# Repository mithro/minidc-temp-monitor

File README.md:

# minidc-temp-monitor

> [!CAUTION]
> **AI in use, use at own risk.**

Cheap temperature monitoring for a **miniature datacenter** with a hot aisle
and a cold aisle. A 42&nbsp;x&nbsp;13 mm **sensor strip board** carries a WCH
RISC-V microcontroller (**CH32V003** or **CH32V005**) and a 100 k NTC
thermistor, with a **JST SH 4-pin** (Qwiic / STEMMA QT style) connector at
each end. Boards daisy-chain on stock cables, and a hub reads the whole chain
over I2C from one end.

A board's address is its position in the chain, so there are no address
straps and the hub sees the boards in their physical order. In a 240-board
build at JLCPCB each board costs $0.30 to $0.33 in parts and $0.58 to $0.97
assembled, before shipping and tax, with the assembly fees calculated from
JLCPCB's published rates.

| `sensor-ch32v003` (SOP-8) | `sensor-ch32v005` (QFN-12) |
| --- | --- |
|  |  |

The KiCad 9 projects are `hardware/sensor-ch32v003` and
`hardware/sensor-ch32v005`. Each has the panel gerbers, parts list and
placement file for an order in `out/panel/`.

Contents:

* [Status](#status)
* [How the chain works](#how-the-chain-works)
* [The two boards](#the-two-boards)
* [What you need](#what-you-need)
* [Getting the boards made](#getting-the-boards-made)
* [Putting a chain together](#putting-a-chain-together)
* [Reading temperatures](#reading-temperatures)
* [Rebuilding the files](#rebuilding-the-files)
* [Further reading](#further-reading)

## Status

| Part | State |
| --- | --- |
| Sensor strip board, v0.2, both versions | drawn, passes ERC and DRC, **not yet built** |
| 16-board assembly panel | drawn, accepted by JLCPCB's and NextPCB's quote pages, not ordered |
| Relay firmware and I2C bootloader | build for both boards and pass tests in a simulated chain, **not yet run on a board** |
| Hub library and command line (`minidc.py`) | tested against the simulated chain only |
| Hub hardware | not designed |
| Humidity sensing | not designed |

Still open: the cable length per aisle and the number of sensor points per
rack face. The known gaps of the board are listed in
[hardware/README.md](hardware/README.md#known-gaps-in-v02), and what the
firmware tests do and do not cover in
[firmware/README.md](firmware/README.md#what-has-been-tested).

## How the chain works

Every cable is its own short I2C bus. On its upstream connector (**J1, UP**) a
board is an I2C target at address `0x2A`. On its downstream connector
(**J2, DN**) it is a bit-banged I2C controller talking to the next board. All
boards use the same address, because each one is alone on its hop.

* **Addressing.** Each command carries a hop count. A board that gets a
  command with a count above zero takes one off and passes it on, and the
  board that sees zero carries it out. Board 0 is the one plugged into the
  hub.
* **Temperatures.** One command reads up to 16 boards in one go, in 0.01 C
  steps. The reading is a ratio of the supply, so it is the same at 3.3 V
  and 5 V.
* **Identify LED.** A command turns on or blinks the LED of one board, to
  find it in the rack.
* **Updates.** Boards take new firmware over the same cable through an I2C
  bootloader, one board at a time.
* **Supply.** 3.3 V or 5 V, passed straight through the chain with no
  regulator on the boards. Never more than 5.5 V.

Because each hop is a fresh bus, cable length does not add up along a chain.
The protocol, the bootloader and the timings are in
[firmware/README.md](firmware/README.md). A shared pass-through bus is a
fitting option on the board
([chain wiring option](hardware/README.md#chain-wiring-option)); the firmware
here is for the relay fitting.

## The two boards

Both versions share the outline, the connectors and every part except the
microcontroller.

| | `sensor-ch32v003` | `sensor-ch32v005` |
| --- | --- | --- |
| Microcontroller | CH32V003J4M6, SOP-8 | CH32V005D6U6, QFN-12 2&nbsp;x&nbsp;2 mm |
| ADC | 10 bit | 12 bit |
| Programming | SWIO test pad | SWIO shares the SCL pin of J1, or the test pad |
| Spare pins | none | two GPIOs and reset on pads |
| Board finish costed | lead-free HASL | ENIG |
| Parts per board | $0.33 | $0.30 |
| 240 boards assembled, JLCPCB | $140 | $233, with X-ray inspection |
| 240 boards assembled, NextPCB | $529 | $651 |

The board has a 3.2 mm hole for an M3 screw, a waist for a zip tie and a flat
back for an adhesive pad or a glued magnet. The thermistor sits on a finger
cut free of the rest of the board. Dimensions, pin use, the copper layout and
the supply voltage limits are in [hardware/README.md](hardware/README.md).

## What you need

### Boards

| Item | Qty | Notes | Details |
| --- | --- | --- | --- |
| Sensor strip board, either version | one per sensor point | Ordered assembled, as panels of 16. | [hardware/README.md](hardware/README.md) |
| Hub | one I2C bus per chain | Anything with a Linux I2C bus (`/dev/i2c-N`), pull-ups on SDA and SCL, and a 3.3 V or 5 V supply for the chain. Every chain needs a bus of its own, and a 200-board build at 3.3 V is at least 10 chains. The pull-ups must suit the chain voltage. | [hub side](firmware/README.md#hub-side), [supply voltage](hardware/README.md#supply-voltage) |
| WCH-LinkE programmer | one | Puts the bootloader and the first application on blank boards. | [programming a blank board](firmware/README.md#programming-a-blank-board) |

### Parts on each board

| Ref | Part | LCSC |
| --- | --- | --- |
| U1 | CH32V003J4M6 or CH32V005D6U6 | C5346354 or C49006243 |
| RT1 | 100 k NTC thermistor, B3950, 1 %, 0402 | C6807762 |
| J1, J2 | JST SH 4-pin, side entry, compatible clone | C7430446 |
| D1 | Red LED, 0603 | C2286 |
| R1, R2, R5, R6, C1 to C3 | Divider, LED and pull-up resistors, decoupling | [full list](hardware/README.md#parts-and-cost) |

### Cables

Generic double-ended JST SH 1.0 mm 4-pin leads from AliExpress, listed at
about $0.10 each, wired straight through: pin 1 at one end reaches pin 1 at
the other. Sellers are expected to call that version "reverse", which is not
confirmed, so check a lead from every lot with a meter. The other version
puts the supply across the wrong pins.

| Lead | Use |
| --- | --- |
| 10, 15 and 20 cm, double-ended | Board to board. The 15 cm lead covers any spacing up to 3U. |
| 30 cm, double-ended | Jumps between rack faces, and a hub with a JST SH socket. |
| 20 cm, single-ended with tinned wires | A hub with pads, pin headers or screw terminals. |

[hardware/CABLES.md](hardware/CABLES.md) has the order list for a 200-board
build (about $41 plus shipping), the listings, and how to tell the two wiring
directions apart.

## Getting the boards made

1. Pick a version. The files are in `hardware/sensor-ch32v003/out/panel/` or
   `hardware/sensor-ch32v005/out/panel/`.
2. Upload `gerbers.zip` to [JLCPCB](https://jlcpcb.com) as a new PCB order
   with the options in the table below.
3. Add assembly, and give it `bom-jlc.csv` and `cpl-jlc.csv` from the same
   folder. They are for the relay fitting.
4. Check the placement preview before paying. The part rotations have not
   been checked against JLCPCB's orientations. On a CH32V005 order, check
   whether X-ray inspection is charged.

| Option | Value |
| --- | --- |
| Size | 107&nbsp;x&nbsp;132 mm panel |
| Panel | "Panel by Customer", 2 columns, 8 rows, 16 boards |
| Quantity | 15 panels |
| Layers | 2 |
| Thickness | 1.6 mm FR-4 |
| Copper | 1 oz |
| Finish | lead-free HASL for the CH32V003, ENIG for the CH32V005 |
| Assembly | Economic, top side, tooling holes "Added by Customer" |

Nobody has placed this order yet. The bare panel price is JLCPCB's online
quote, and its assembly step, which needs a sign-in, has not been reached.

15 panels make 240 boards. [hardware/COST.md](hardware/COST.md) has the cost
line by line, and [hardware/QUOTES.md](hardware/QUOTES.md) compares the
JLCPCB and NextPCB quotes and says which figures are quoted and which are
calculated. The files for NextPCB's quote page are in
`hardware/sensor-*/out/nextpcb/`. The panel itself is described in
[hardware/README.md](hardware/README.md#panel).

## Putting a chain together

1. **Program each board.** Write the bootloader, the application and the
   option word through the SWIO pad with a WCH-LinkE, as in
   [programming a blank board](firmware/README.md#programming-a-blank-board).
   The option word for the CH32V005 has not been checked on a real part. A
   board with no firmware does not pass the bus on, so the chain stops
   there.
2. **Check the cables.** Test one lead from every lot between two unpowered
   boards with a meter before powering anything
   ([wiring direction](hardware/CABLES.md#wiring-direction)).
3. **Chain the boards.** The hub goes to **J1 (UP)** of the first board, and
   each **J2 (DN)** goes to J1 of the next board.
4. **Power it.** One chain runs at one voltage. Keep a 3.3 V chain to about
   20 boards; a 5 V chain can be longer and must have a regulated supply
   ([supply voltage](hardware/README.md#supply-voltage),
   [chain head and hub](hardware/CABLES.md#chain-head-and-hub)). Connect
   the hub before powering the chain: with nothing on J1 of the first board
   the boards may wait in their bootloaders until `minidc.py boot` starts
   them. With CH32V005 boards, keep the hub quiet on the bus for the first
   second after power-on ([bootloader](firmware/README.md#bootloader)).
5. **Find each board.** Scan the chain and blink a board's LED with the
   [hub commands](#reading-temperatures), and write its position in the
   white box on the back.

| Pin of J1 and J2 | Signal |
| --- | --- |
| 1 | GND |
| 2 | VDD, 3.3 V or 5 V |
| 3 | SDA |
| 4 | SCL |

## Reading temperatures

`firmware/tools/minidc.py` is a reference hub in Python, standard library
only. It is a `Chain` class to import and a command line over Linux
`/dev/i2c-N`:

```
python3 firmware/tools/minidc.py --bus 1 scan
python3 firmware/tools/minidc.py --bus 1 temps
python3 firmware/tools/minidc.py --bus 1 led 7 blink 30
python3 firmware/tools/minidc.py --bus 1 update 7 firmware/build/relay-ch32v003.bin
```

A simulated 200-board chain reads in about 21 s at the default 10 kHz per
hop. The hub must end every write with a STOP before it reads, and tolerate
short clock stretching by the first board. The commands, status codes and the update procedure
are in [firmware/README.md](firmware/README.md#protocol).

## Rebuilding the files

The KiCad files are generated by the scripts in `hardware/scripts/`, so
change the scripts and rebuild rather than editing the boards by hand. This
needs KiCad 9, Pillow, openpyxl, the DejaVu fonts and zip:

```
hardware/build.sh
```

It redraws both schematics, boards and panels, runs ERC and DRC, and rewrites
the exports, the renders and `COST.md`.

The firmware builds with GCC for RISC-V and the
[ch32fun](https://github.com/cnlohr/ch32fun) SDK:

```
sudo apt install gcc-riscv64-unknown-elf libnewlib-dev make python3
git submodule update --init firmware/ch32fun
make -C firmware          # images in firmware/build/
make -C firmware test     # host tests
```

CI builds the firmware and runs its tests on every firmware change.

## Further reading

* [Hardware](hardware/README.md): schematics, dimensioned renders, the
  copper layout, the panel, the parts list, supply voltage limits, the chain
  wiring option, notes for firmware and the known gaps.
* [Cost](hardware/COST.md): the price of 240 boards of each version, line by
  line.
* [Production quotes](hardware/QUOTES.md): JLCPCB against NextPCB, and how
  each figure was obtained.
* [Cables](hardware/CABLES.md): what to order, which wiring direction, and
  the lengths for each board spacing.
* [Firmware](firmware/README.md): how the relay works, the protocol, the
  bootloader, recovery, programming a blank board and what has been tested.
* [Research](docs/README.md): surveys of cheap I2C temperature sensors, the
  Qwiic and related connector ecosystems, and JST SH 4-pin connectors and
  their clones.

## Licence

Apache 2.0. See [LICENSE](LICENSE).

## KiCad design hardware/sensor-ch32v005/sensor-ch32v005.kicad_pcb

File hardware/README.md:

# Hardware: temperature sensor strip, v0.2

A small pass-through board for a chain of temperature sensors on a Qwiic style
(JST SH 4-pin) I2C cable. Each board carries a WCH RISC-V microcontroller that
reads a 100 k NTC thermistor and answers on I2C. A board's address is its
position in the chain, so there are no strap resistors. The firmware is in
[../firmware/](../firmware/README.md).

There are two versions of the same board, differing only in the microcontroller:

| | `sensor-ch32v003` | `sensor-ch32v005` |
|---|---|---|
| MCU | CH32V003J4M6, SOP-8 (LCSC C5346354) | CH32V005D6U6, QFN-12 2x2 mm (LCSC C49006243) |
| ADC | 10 bit | 12 bit |
| Upstream I2C (to J1) | hardware I2C on PC1/PC2 | hardware I2C on PD0/PD1 (remap 1) |
| Downstream I2C (to J2) | bit-banged on PC4 (SDA) and PA2 (SCL) | bit-banged on PC0/PC3 |
| Thermistor divider | fed from VDD, read on PA1 (pin 1, shared with PD6) | fed from PC6 while sampling, read on PC4 |
| Identify LED | shares the SWIO pin (PD1/PD4/PD5) | PA2 |
| Programming | SWIO test pad TP1 | SWIO is the SCL pin, so J1 pin 4 or TP1 |
| Spare pins | none | PA1, PC7 and reset on 1 mm pads (PA1, PC7, RST) |

## Schematic and board

| | Schematic | Board | Parts list | Placement | Checks |
|---|---|---|---|---|---|
| `sensor-ch32v003` | [PDF](sensor-ch32v003/out/schematic.pdf) | [3D views](sensor-ch32v003/out/board-3d.png), [gerbers](sensor-ch32v003/out/gerbers/) | [BOM](sensor-ch32v003/out/bom-jlc.csv) | [CPL](sensor-ch32v003/out/cpl-jlc.csv) | [ERC](sensor-ch32v003/out/erc.rpt), [DRC](sensor-ch32v003/out/drc.rpt) |
| `sensor-ch32v005` | [PDF](sensor-ch32v005/out/schematic.pdf) | [3D views](sensor-ch32v005/out/board-3d.png), [gerbers](sensor-ch32v005/out/gerbers/) | [BOM](sensor-ch32v005/out/bom-jlc.csv) | [CPL](sensor-ch32v005/out/cpl-jlc.csv) | [ERC](sensor-ch32v005/out/erc.rpt), [DRC](sensor-ch32v005/out/drc.rpt) |

The renders below are made by `scripts/render.py` from the board files. The
dimensions on them are read from the board, not typed in.

| | |
|---|---|
| Outline | 42.0 x 13.0 mm, 1.6 mm thick, two layers, 4.6 mm tall over the connectors |
| Parts | top side only; the back is flat for an adhesive pad or a glued magnet |
| J1 (UP), J2 (DN) | JST SH 1.0 mm 4-pin, side entry, facing out of the short edges. Pin 1 GND, 2 VDD, 3 SDA, 4 SCL |
| Mounting hole | 3.2 mm for M3, 11.5 mm from the J1 end, on the centre line, with a 7.2 mm copper-free washer area on both sides |
| Zip-tie waist | 3.0 mm wide, 1.2 mm deep notch in each long edge, 14 to 17 mm from the J1 end |
| Thermistor finger | 2.6 mm wide, 7.0 mm long, cut free by a 1.5 mm slot, no copper pour, RT1 near the tip |
| Test pads | GND, VDD and SWIO: 1.5 mm pads in a column on 2.54 mm pitch, to take a 3-pin pogo clip or header |
| Back | board name and revision, the two chain fittings, and a white box to write the board's address on |

How the copper is laid out:

- The top layer carries every signal. The back is a ground plane crossed by
  one track only: a 0.8 mm VDD trunk from J1 to J2. The microcontroller taps
  the trunk through a via at its decoupling capacitor, so chain current does
  not pass through the microcontroller's supply pad.
- Each connector power pin has two vias. Stitching vias tie the top ground
  pour to the plane.
- R3 to R6 are 0603 so that each can bridge a track on the top layer. That is
  what keeps the back plane whole.
- Copper stays 0.5 mm from every board edge, and 1.0 mm back where the panel
  tabs attach. `gen_pcb.py` checks the pour against the edge on every build,
  because KiCad's DRC does not.
- The CH32V005's only ground is its exposed pad. It has one via in a corner of
  the pad, and solder paste on the rest (60 % of the pad).
- Fabrication class: 0.2 mm tracks, 0.6/0.3 mm vias (0.5/0.3 mm under the
  CH32V005), which is JLCPCB's cheapest two-layer class.

## Panel

JLCPCB assembles small boards as a panel. `scripts/gen_panel.py` builds one for
each version: 16 boards (2 x 8) in a 107 x 132 mm frame. The quotes are for
15 panels, 240 boards.

| | Panel board | Gerbers | Parts list | Placement | Check |
|---|---|---|---|---|---|
| `sensor-ch32v003` | [KiCad](sensor-ch32v003/sensor-ch32v003-panel.kicad_pcb) | [zip](sensor-ch32v003/out/panel/gerbers.zip) | [BOM](sensor-ch32v003/out/panel/bom-jlc.csv) | [CPL](sensor-ch32v003/out/panel/cpl-jlc.csv) | [DRC](sensor-ch32v003/out/panel/drc.rpt) |
| `sensor-ch32v005` | [KiCad](sensor-ch32v005/sensor-ch32v005-panel.kicad_pcb) | [zip](sensor-ch32v005/out/panel/gerbers.zip) | [BOM](sensor-ch32v005/out/panel/bom-jlc.csv) | [CPL](sensor-ch32v005/out/panel/cpl-jlc.csv) | [DRC](sensor-ch32v005/out/panel/drc.rpt) |

| | |
|---|---|
| Frame | 5 mm rails on all four sides and a 5 mm rail between the two columns |
| Between boards | 2 mm routed slots |
| Tabs | six per board. Four are 5 mm wide, on the long edges 7.0 and 37.5 mm from the J1 end, to the boards above and below. Two are 2 mm wide, at the top corner of each short edge clear of the connector, to the rail beside the board |
| Mouse bites | 0.6 mm holes on 1.0 mm pitch along each tab's board edge, centred 0.05 mm inside the edge, 0.6 mm or more from copper |
| Fiducials | three on the top and bottom rails, 1 mm copper in a 2 mm mask opening, in the middle of the rail |
| Tooling holes | four, 1.152 mm, unplated, 2.5 mm from the panel corners |
| Designators | each part's own designator plus the board number, for example `R5_07` |

To order: upload `gerbers.zip`, choose "Panel by Customer" with 16 boards per
panel, and give the panel BOM and CPL to the assembly step. The panel is
separated by mouse bites, not V-cuts, because the outline has notches and a
slot and the parts sit close to the edges.

The JLCPCB figures used here (rail width, fiducial and tooling hole sizes,
mouse-bite hole size and spacing) come from JLCPCB's help pages as found on
18 Nov 2026. Their pages do not agree with each other on every number, so
check the panel in JLCPCB's order preview before paying. Both JLCPCB's and
NextPCB's quote pages read the panel gerbers without errors
([QUOTES.md](QUOTES.md)).

## Parts and cost

Both boards share every part except the microcontroller. Prices are JLCPCB
catalogue prices on 18 Nov 2026 for 240 boards; [COST.md](COST.md) has the full calculation,
with the quoted panel price and the assembly fees. [QUOTES.md](QUOTES.md)
compares the JLCPCB and NextPCB production quotes.

| Ref | Part | LCSC | Fitted |
|---|---|---|---|
| U1 | CH32V003J4M6 or CH32V005D6U6 | C5346354 or C49006243 | yes |
| RT1 | 100k NTC, B3950, 1%, 0402 (Sunlord SDNT1005X104F3950FTF) | C6807762 | yes |
| R1 | 100k 1% 0402, divider | C25741 | yes |
| R2 | 1k 0402, LED | C11702 | yes |
| R3, R4 | 0R 0603, shared-bus links | C21189 | no |
| R5, R6 | 4k7 1% 0603, downstream pull-ups | C23162 | yes, optional |
| C1, C3 | 100n 16 V X7R 0402 | C1525 | yes |
| C2 | 1u 25 V X5R 0402 | C52923 | yes |
| D1 | Red LED 0603 | C2286 | yes |
| J1, J2 | JST SH 4-pin, side entry, compatible clone | C7430446 | yes |

| | `sensor-ch32v003` | `sensor-ch32v005` |
|---|---|---|
| Parts per board | $0.33 | $0.30 |
| 240 boards assembled, JLCPCB | $140 (lead-free HASL) | $233 (ENIG, X-ray) |
| 240 boards assembled, NextPCB | $529 (lead-free HASL) | $651 (ENIG) |

## Cables

Generic double-ended JST SH 1.0 mm 4-pin leads from AliExpress, listed at about
$0.10 each, wired straight through: pin 1 at one end must reach pin 1 at the other.
[CABLES.md](CABLES.md) has the order list, the lengths, how to tell the two
wiring directions apart, and the leads for the hub end of each chain.

## Supply voltage

The boards run from 3.3 V or 5 V on VDD (J1/J2 pin 2) with no fitting change.
There is no regulator: VDD feeds the microcontroller directly and passes
straight through to the next board, so one chain runs at one voltage.

| | At 3.3 V | At 5 V | Limit |
|---|---|---|---|
| CH32V003 supply | ok | ok | 2.7 to 5.5 V, 2.8 V or more for the ADC |
| CH32V005 supply | ok | ok | 2.0 to 5.5 V, 2.4 V or more for the ADC |
| C1, C3 (100n) and C2 (1u) | ok | ok | rated 16 V and 25 V |
| Identify LED through R2 (1k) | about 1.4 mA | about 3 mA | 20 mA |
| R5, R6 pull-up current (4k7) | 0.7 mA | 1.1 mA | 3 mA for standard I2C |
| Thermistor self-heating at 25 C | about 27 uW | about 63 uW | negligible |

- The thermistor reading is ratiometric. The divider and the ADC reference both
  hang off VDD (through PC6 on the CH32V005), so the reading does not depend on
  the supply voltage. Firmware must work from the ADC ratio and never assume a
  VDD value.
- Never put more than 5.5 V on VDD. That is both the operating and the absolute
  maximum of the microcontrollers, and there is no protection on the board, so
  a 5 V supply must be a regulated one.
- 5 V leaves far more room for voltage drop along a long chain than 3.3 V does
  (2.2 V against 0.5 V before the CH32V003 ADC limit).
- The hub must suit the chain voltage. The simple case is hub pull-ups to the
  same rail as VDD. A 3.3 V hub can also drive a 5 V chain if its pull-ups go
  to 3.3 V, because both microcontrollers read 3.3 V as high at VDD = 5 V
  (input high threshold about 2.1 V on the CH32V003 and 2.2 V on the
  CH32V005). That relies on the boards never driving SDA or SCL high, so
  firmware must only ever pull the upstream I2C pins low or release them. Do not pull the bus up to 5 V on
  a 3.3 V chain.
- No signal may go above VDD. The CH32V005 has no 5 V tolerant pins, and on the
  CH32V003 only the upstream I2C pins are. Set the debug probe to the chain
  voltage or lower: a 3.3 V probe works on a 5 V board, a 5 V probe on a 3.3 V
  board does not.
- Qwiic and STEMMA QT cables and the JST SH connectors carry either voltage,
  but standard Qwiic boards are 3.3 V only. Do not plug one into a 5 V chain.

## Chain wiring option

| Mode | R3, R4 (0R) | R5, R6 (4k7) | Behaviour |
|---|---|---|---|
| Relay (default) | not fitted | fitted (optional) | Each board is an I2C target upstream and a bit-banged controller downstream, and forwards traffic. Every hop is a fresh, short bus. |
| Shared bus | fitted | not fitted | SDA/SCL pass straight through. All boards share one bus. |

R5 and R6 are optional. The microcontrollers have internal pull-ups of 35 to
55 k, which carry a short hop at roughly 10 to 20 kHz, so a relay board also
works with R5 and R6 left off. With them fitted a hop runs at 100 kHz and holds
the bus better against noise. They are in the BOM and placement files; delete
their rows from both to build without them.

The BOM and placement files are for the relay fitting. R5 and R6 are the pull-ups
of the hop to the next board; the hop from the hub to the first board uses the
pull-ups on the hub. In shared-bus mode no pull-ups are fitted on the boards.

A relay-fitted board with no firmware does not pass the bus on, so the chain
stops at the first unprogrammed board.

## Files

Everything is generated by the scripts, so change the scripts and rebuild rather
than editing the KiCad files by hand (hand edits are lost on the next build).

- `scripts/gen_sch.py` draws the schematic and checks it against its pin table.
  It also writes `lib/minidc.kicad_sym` (the MCU symbols, adjusted so pin text
  does not collide) and the `sym-lib-table` in each project directory.
- `scripts/layout.py` is the board layout itself: where every part, track,
  via and label goes, in millimetres from the board's top left corner.
- `scripts/gen_pcb.py` builds the board file from the schematic's netlist and
  `layout.py`, and pours ground.
- `scripts/gen_panel.py` builds the assembly panel and its parts list.
- `scripts/render.py` draws the dimensioned 3D views.
- `scripts/gen_models.py` writes the two 3D models KiCad's library lacks (the
  connector and the QFN-12) into `3dmodels/`, which also holds the stock KiCad
  models the renders use.
- `scripts/cost.py` prices both boards from their parts lists and writes
  [COST.md](COST.md).
- `scripts/gen_nextpcb.py` writes the parts list and placement file in the
  form NextPCB's quote page takes, into `sensor-*/out/nextpcb/`.
- `build.sh` runs all of the above for both versions, with ERC and DRC, and
  stops if either reports anything.
- `sensor-*/out/` holds the schematic PDF, the 3D views, gerbers, the BOM and
  placement files in JLCPCB column layout, and the ERC and DRC reports.
  `sensor-*/out/panel/` holds the panel's gerbers (zipped), a render, its BOM
  and placement files and its DRC report. `sensor-*/out/nextpcb/` holds the
  NextPCB parts list and placement spreadsheets.
- `scripts/sexp.py` is a small reader for KiCad's file format, used by the
  other scripts.

Needs KiCad 9 (`kicad-cli`, the `pcbnew` Python module and the stock footprint
library), Pillow, openpyxl, the DejaVu fonts and zip.

## Notes for firmware

- CH32V005: SCL to J1 is also SWIO, and the debug interface is on after reset.
  Firmware must wait a moment at boot before turning it off and enabling I2C,
  or the board cannot be reflashed. In shared-bus mode R4 joins every board's
  SWIO, so flash a board on its own.
- CH32V005: the divider is powered from PC6. Wait about 25 ms after driving PC6
  high before sampling, so C3 has settled.
- CH32V003: the LED sits on the SWIO pin. Light it by driving PD4 or PD5 low and
  leave PD1 as SWIO. Pin 1 is PD6 and PA1 bonded together and is the thermistor
  input: read it as ADC channel 1 (PA1) and keep PD6 an input.
- R5 and R6 are optional, so in relay mode firmware must work the downstream
  SDA and SCL pins without them: release a line by making the pin an input with
  its pull-up on, and drive it by making the pin an output held low. The
  internal pull-up only exists in input mode. Pick the downstream bit rate to
  suit: 10 to 20 kHz on internal pull-ups alone, up to 100 kHz with R5 and R6.
  Keep the pull-ups off on the upstream pins, and on every bus pin in
  shared-bus mode, so the only pull-ups there are the ones on the hub.
- CH32V003: the ADC and flash writes want VDD of 2.8 V or more, and ADC accuracy
  is only specified above 2.9 V. Watch the drop on long chains, mainly at 3.3 V.
- The allowed ADC speed depends on VDD. Keep the CH32V003 ADC clock at 6 MHz or
  less and the CH32V005 sample rate at 1 MHz or less, so one firmware covers
  both voltages.

## Known gaps in v0.2

- The [firmware](../firmware/README.md) has not run on a board. The relay, the
  bootloader and the CH32V005 programming window on the shared SCL/SWIO pin
  are tested in simulation only.
- Running without R5 and R6 is untested. Try a few boards with them removed
  before leaving them off a whole build.
- The placement file rotations have not been checked against JLCPCB's part
  orientations. Check the preview when ordering.
- Silkscreen text is 0.8 mm high with a 0.15 mm stroke. JLCPCB's capability
  page asks for 1.0 mm, and there is no room for that on this board, so some
  designators may print soft.
- On the CH32V003 board C1, C2, C3 and R1 have no designator: there is no room
  beside them. From the top they are R1, C3, C2, C1 in the column left of U1.
- CH32V005: the ground via sits in the exposed pad and is open on the top
  side, so some solder can run into it. The QFN is 0.4 mm pitch, so the
  CH32V005 board is costed with ENIG, which adds about 0.08 per board at
  JLCPCB ([QUOTES.md](QUOTES.md)).
- The panel follows JLCPCB's published rules as far as they could be read.
  JLCPCB's and NextPCB's quote pages accepted the gerbers, but JLCPCB's
  placement preview, which needs a sign-in, has not been seen and nobody at
  JLCPCB has reviewed the panel.
- JLCPCB's assembly price is calculated from its published fees, not quoted.
  Its fee list charges X-ray inspection per QFN, about 79 for 240 CH32V005
  boards; the signed-in quote will show whether that applies.
- On the CH32V005 board the SDA line leaves J1 under the connector housing.
  The stock footprint has no copper there, but the fit under the clone part
  has not been checked on a real board.
- The JST SH connector part is a compatible clone (LCSC C7430446). Its drawing
  shows the leads and mounting tabs landing on the JST footprint used here (see the
  [connector survey](../docs/research/jst-sh-4pin-connectors.md#land-pattern-of-the-fitted-part)),
  but no part has been soldered to the footprint or mated with a cable yet.

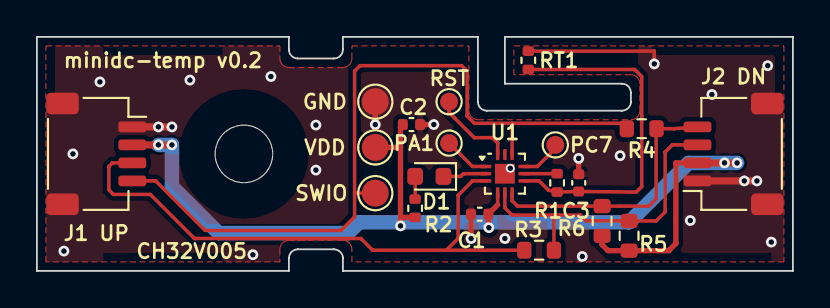
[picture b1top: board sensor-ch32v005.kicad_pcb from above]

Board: 2 copper layers, 42.0 x 13.0 mm, 21 parts (0 on the bottom side), 13 nets.

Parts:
C1, C3: 100n; C_0402_1005Metric
C2: 1u; C_0402_1005Metric
D1: RED; LED_0603_1608Metric
H1: M3; MountingHole_3.2mm_M3
J1: Qwiic UP; JST_SH_SM04B-SRSS-TB_1x04-1MP_P1.00mm_Horizontal
J2: Qwiic DOWN; JST_SH_SM04B-SRSS-TB_1x04-1MP_P1.00mm_Horizontal
R1: 100k 1%; R_0402_1005Metric
R2: 1k; R_0402_1005Metric
R3, R4: 0R; R_0603_1608Metric
R5, R6: 4k7; R_0603_1608Metric
RT1: 100k B3950 1%; R_0402_1005Metric
TP1: SWIO; TestPoint_Pad_D1.5mm
TP2: VDD; TestPoint_Pad_D1.5mm
TP3: GND; TestPoint_Pad_D1.5mm
TP4: NRST; TestPoint_Pad_D1.0mm
TP5: AUX_A1; TestPoint_Pad_D1.0mm
TP6: AUX_PC7; TestPoint_Pad_D1.0mm
U1: CH32V005D6U6; UQFN-12-1EP_2x2mm_P0.4mm_EP1.1x1.1mm

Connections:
/AUX_A1: TP5.1, U1.1
/AUX_PC7: TP6.1, U1.9
/LED_K: D1.1, U1.2
/NRST: TP4.1, U1.12
/NTC_ADC: C3.1, R1.2, RT1.1, U1.7
/NTC_DRV: R1.1, U1.8
/SCL_DN: J2.4, R4.2, R6.2, U1.6
/SCL_UP: J1.4, R4.1, TP1.1, U1.10
/SDA_DN: J2.3, R3.2, R5.2, U1.5
/SDA_UP: J1.3, R3.1, U1.3
GND: C1.2, C2.2, C3.2, J1.1, J1.MP, J2.1, J2.MP, RT1.2, TP3.1, U1.13
unnamed: D1.2, R2.2
VDD: C1.1, C2.1, J1.2, J2.2, R2.1, R5.1, R6.1, TP2.1, U1.4

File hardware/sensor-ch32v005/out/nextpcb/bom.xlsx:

S/N | Designator | Quantity | Manufacturer Part Number | Procurement Type | Customer Note
1 | C2 | 1 | CL05A105KA5NQNC |  | 1u
2 | C1,C3 | 2 | CL05B104KO5NNNC |  | 100n
3 | D1 | 1 | KT-0603R |  | RED
4 | J1,J2 | 2 | ZX-SH1.0-4PWT |  | Qwiic UP
5 | R1 | 1 | 0402WGF1003TCE |  | 100k 1%
6 | R2 | 1 | 0402WGF1001TCE |  | 1k
7 | R5,R6 | 2 | 0603WAF4701T5E |  | 4k7
8 | RT1 | 1 | SDNT1005X104F3950FTF |  | 100k B3950 1%
9 | U1 | 1 | CH32V005D6U6 |  | CH32V005D6U6

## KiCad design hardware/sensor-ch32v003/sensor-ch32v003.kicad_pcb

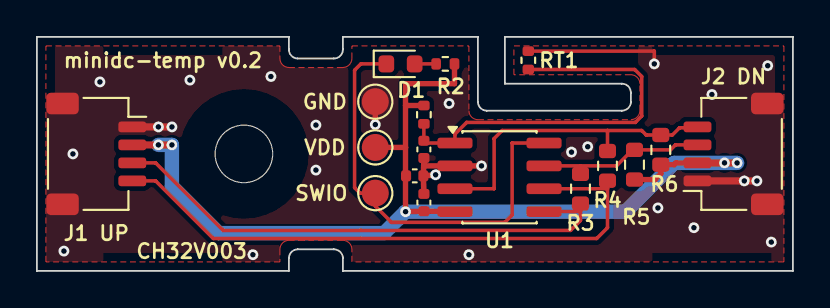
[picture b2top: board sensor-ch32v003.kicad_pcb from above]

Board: 2 copper layers, 42.0 x 13.0 mm, 18 parts (0 on the bottom side), 9 nets.

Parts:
C1, C3: 100n; C_0402_1005Metric
C2: 1u; C_0402_1005Metric
D1: RED; LED_0603_1608Metric
H1: M3; MountingHole_3.2mm_M3
J1: Qwiic UP; JST_SH_SM04B-SRSS-TB_1x04-1MP_P1.00mm_Horizontal
J2: Qwiic DOWN; JST_SH_SM04B-SRSS-TB_1x04-1MP_P1.00mm_Horizontal
R1: 100k 1%; R_0402_1005Metric
R2: 1k; R_0402_1005Metric
R3, R4: 0R; R_0603_1608Metric
R5, R6: 4k7; R_0603_1608Metric
RT1: 100k B3950 1%; R_0402_1005Metric
TP1: SWIO; TestPoint_Pad_D1.5mm
TP2: VDD; TestPoint_Pad_D1.5mm
TP3: GND; TestPoint_Pad_D1.5mm
U1: CH32V003J4M6; SOIC-8_3.9x4.9mm_P1.27mm

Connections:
/NTC_ADC: C3.1, R1.2, RT1.1, U1.1
/SCL_DN: J2.4, R4.2, R6.2, U1.3
/SCL_UP: J1.4, R4.1, U1.6
/SDA_DN: J2.3, R3.2, R5.2, U1.7
/SDA_UP: J1.3, R3.1, U1.5
/SWIO: D1.1, TP1.1, U1.8
GND: C1.2, C2.2, C3.2, J1.1, J1.MP, J2.1, J2.MP, RT1.2, TP3.1, U1.2
unnamed: D1.2, R2.2
VDD: C1.1, C2.1, J1.2, J2.2, R1.1, R2.1, R5.1, R6.1, TP2.1, U1.4

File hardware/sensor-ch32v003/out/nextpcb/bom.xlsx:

S/N | Designator | Quantity | Manufacturer Part Number | Procurement Type | Customer Note
1 | C2 | 1 | CL05A105KA5NQNC |  | 1u
2 | C1,C3 | 2 | CL05B104KO5NNNC |  | 100n
3 | D1 | 1 | KT-0603R |  | RED
4 | J1,J2 | 2 | ZX-SH1.0-4PWT |  | Qwiic UP
5 | R1 | 1 | 0402WGF1003TCE |  | 100k 1%
6 | R2 | 1 | 0402WGF1001TCE |  | 1k
7 | R5,R6 | 2 | 0603WAF4701T5E |  | 4k7
8 | RT1 | 1 | SDNT1005X104F3950FTF |  | 100k B3950 1%
9 | U1 | 1 | CH32V003J4M6 |  | CH32V003J4M6

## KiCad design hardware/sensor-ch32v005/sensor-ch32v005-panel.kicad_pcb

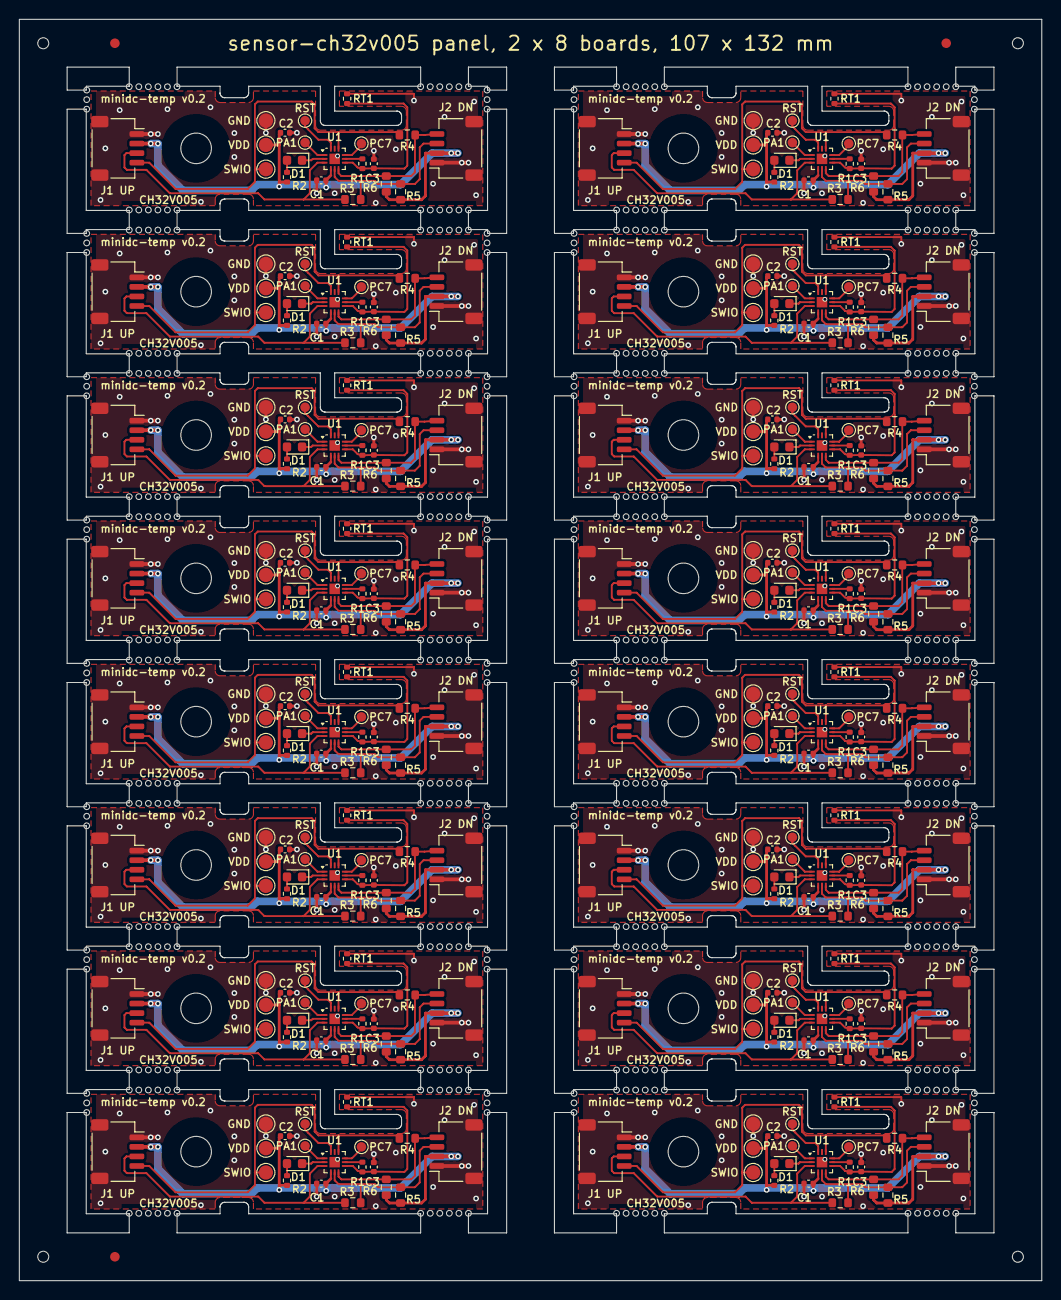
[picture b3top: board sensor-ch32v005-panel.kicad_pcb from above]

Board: 2 copper layers, 107.0 x 132.0 mm, 336 parts (0 on the bottom side), 208 nets.

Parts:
C1_01, C1_02, C1_03, C1_04, C1_05, C1_06, C1_07, C1_08, C1_09, C1_10, C1_11, C1_12, C1_13, C1_14, C1_15, C1_16, C3_01, C3_02, C3_03, C3_04, C3_05, C3_06, C3_07, C3_08, C3_09, C3_10, C3_11, C3_12, C3_13, C3_14, C3_15, C3_16: 100n; C_0402_1005Metric
C2_01, C2_02, C2_03, C2_04, C2_05, C2_06, C2_07, C2_08, C2_09, C2_10, C2_11, C2_12, C2_13, C2_14, C2_15, C2_16: 1u; C_0402_1005Metric
D1_01, D1_02, D1_03, D1_04, D1_05, D1_06, D1_07, D1_08, D1_09, D1_10, D1_11, D1_12, D1_13, D1_14, D1_15, D1_16: RED; LED_0603_1608Metric
H1_01, H1_02, H1_03, H1_04, H1_05, H1_06, H1_07, H1_08, H1_09, H1_10, H1_11, H1_12, H1_13, H1_14, H1_15, H1_16: M3; MountingHole_3.2mm_M3
J1_01, J1_02, J1_03, J1_04, J1_05, J1_06, J1_07, J1_08, J1_09, J1_10, J1_11, J1_12, J1_13, J1_14, J1_15, J1_16: Qwiic UP; JST_SH_SM04B-SRSS-TB_1x04-1MP_P1.00mm_Horizontal
J2_01, J2_02, J2_03, J2_04, J2_05, J2_06, J2_07, J2_08, J2_09, J2_10, J2_11, J2_12, J2_13, J2_14, J2_15, J2_16: Qwiic DOWN; JST_SH_SM04B-SRSS-TB_1x04-1MP_P1.00mm_Horizontal
R1_01, R1_02, R1_03, R1_04, R1_05, R1_06, R1_07, R1_08, R1_09, R1_10, R1_11, R1_12, R1_13, R1_14, R1_15, R1_16: 100k 1%; R_0402_1005Metric
R2_01, R2_02, R2_03, R2_04, R2_05, R2_06, R2_07, R2_08, R2_09, R2_10, R2_11, R2_12, R2_13, R2_14, R2_15, R2_16: 1k; R_0402_1005Metric
R3_01, R3_02, R3_03, R3_04, R3_05, R3_06, R3_07, R3_08, R3_09, R3_10, R3_11, R3_12, R3_13, R3_14, R3_15, R3_16, R4_01, R4_02, R4_03, R4_04, R4_05, R4_06, R4_07, R4_08, R4_09, R4_10, R4_11, R4_12, R4_13, R4_14, R4_15, R4_16: 0R; R_0603_1608Metric
R5_01, R5_02, R5_03, R5_04, R5_05, R5_06, R5_07, R5_08, R5_09, R5_10, R5_11, R5_12, R5_13, R5_14, R5_15, R5_16, R6_01, R6_02, R6_03, R6_04, R6_05, R6_06, R6_07, R6_08, R6_09, R6_10, R6_11, R6_12, R6_13, R6_14, R6_15, R6_16: 4k7; R_0603_1608Metric
RT1_01, RT1_02, RT1_03, RT1_04, RT1_05, RT1_06, RT1_07, RT1_08, RT1_09, RT1_10, RT1_11, RT1_12, RT1_13, RT1_14, RT1_15, RT1_16: 100k B3950 1%; R_0402_1005Metric
TP1_01, TP1_02, TP1_03, TP1_04, TP1_05, TP1_06, TP1_07, TP1_08, TP1_09, TP1_10, TP1_11, TP1_12, TP1_13, TP1_14, TP1_15, TP1_16: SWIO; TestPoint_Pad_D1.5mm
TP2_01, TP2_02, TP2_03, TP2_04, TP2_05, TP2_06, TP2_07, TP2_08, TP2_09, TP2_10, TP2_11, TP2_12, TP2_13, TP2_14, TP2_15, TP2_16: VDD; TestPoint_Pad_D1.5mm
TP3_01, TP3_02, TP3_03, TP3_04, TP3_05, TP3_06, TP3_07, TP3_08, TP3_09, TP3_10, TP3_11, TP3_12, TP3_13, TP3_14, TP3_15, TP3_16: GND; TestPoint_Pad_D1.5mm
TP4_01, TP4_02, TP4_03, TP4_04, TP4_05, TP4_06, TP4_07, TP4_08, TP4_09, TP4_10, TP4_11, TP4_12, TP4_13, TP4_14, TP4_15, TP4_16: NRST; TestPoint_Pad_D1.0mm
TP5_01, TP5_02, TP5_03, TP5_04, TP5_05, TP5_06, TP5_07, TP5_08, TP5_09, TP5_10, TP5_11, TP5_12, TP5_13, TP5_14, TP5_15, TP5_16: AUX_A1; TestPoint_Pad_D1.0mm
TP6_01, TP6_02, TP6_03, TP6_04, TP6_05, TP6_06, TP6_07, TP6_08, TP6_09, TP6_10, TP6_11, TP6_12, TP6_13, TP6_14, TP6_15, TP6_16: AUX_PC7; TestPoint_Pad_D1.0mm
U1_01, U1_02, U1_03, U1_04, U1_05, U1_06, U1_07, U1_08, U1_09, U1_10, U1_11, U1_12, U1_13, U1_14, U1_15, U1_16: CH32V005D6U6; UQFN-12-1EP_2x2mm_P0.4mm_EP1.1x1.1mm

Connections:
B01/AUX_A1: TP5_01.1, U1_01.1
B01/AUX_PC7: TP6_01.1, U1_01.9
B01/GND: C1_01.2, C2_01.2, C3_01.2, J1_01.1, J1_01.MP, J2_01.1, J2_01.MP, RT1_01.2, TP3_01.1, U1_01.13
B01/LED_K: D1_01.1, U1_01.2
B01/NRST: TP4_01.1, U1_01.12
B01/NTC_ADC: C3_01.1, R1_01.2, RT1_01.1, U1_01.7
B01/NTC_DRV: R1_01.1, U1_01.8
B01/Net-(D1-A): D1_01.2, R2_01.2
B01/SCL_DN: J2_01.4, R4_01.2, R6_01.2, U1_01.6
B01/SCL_UP: J1_01.4, R4_01.1, TP1_01.1, U1_01.10
B01/SDA_DN: J2_01.3, R3_01.2, R5_01.2, U1_01.5
B01/SDA_UP: J1_01.3, R3_01.1, U1_01.3
B01/VDD: C1_01.1, C2_01.1, J1_01.2, J2_01.2, R2_01.1, R5_01.1, R6_01.1, TP2_01.1, U1_01.4
B02/AUX_A1: TP5_02.1, U1_02.1
B02/AUX_PC7: TP6_02.1, U1_02.9
B02/GND: C1_02.2, C2_02.2, C3_02.2, J1_02.1, J1_02.MP, J2_02.1, J2_02.MP, RT1_02.2, TP3_02.1, U1_02.13
B02/LED_K: D1_02.1, U1_02.2
B02/NRST: TP4_02.1, U1_02.12
B02/NTC_ADC: C3_02.1, R1_02.2, RT1_02.1, U1_02.7
B02/NTC_DRV: R1_02.1, U1_02.8
B02/Net-(D1-A): D1_02.2, R2_02.2
B02/SCL_DN: J2_02.4, R4_02.2, R6_02.2, U1_02.6
B02/SCL_UP: J1_02.4, R4_02.1, TP1_02.1, U1_02.10
B02/SDA_DN: J2_02.3, R3_02.2, R5_02.2, U1_02.5
B02/SDA_UP: J1_02.3, R3_02.1, U1_02.3
B02/VDD: C1_02.1, C2_02.1, J1_02.2, J2_02.2, R2_02.1, R5_02.1, R6_02.1, TP2_02.1, U1_02.4
B03/AUX_A1: TP5_03.1, U1_03.1
B03/AUX_PC7: TP6_03.1, U1_03.9
B03/GND: C1_03.2, C2_03.2, C3_03.2, J1_03.1, J1_03.MP, J2_03.1, J2_03.MP, RT1_03.2, TP3_03.1, U1_03.13
B03/LED_K: D1_03.1, U1_03.2
B03/NRST: TP4_03.1, U1_03.12
B03/NTC_ADC: C3_03.1, R1_03.2, RT1_03.1, U1_03.7
B03/NTC_DRV: R1_03.1, U1_03.8
B03/Net-(D1-A): D1_03.2, R2_03.2
B03/SCL_DN: J2_03.4, R4_03.2, R6_03.2, U1_03.6
B03/SCL_UP: J1_03.4, R4_03.1, TP1_03.1, U1_03.10
B03/SDA_DN: J2_03.3, R3_03.2, R5_03.2, U1_03.5
B03/SDA_UP: J1_03.3, R3_03.1, U1_03.3
B03/VDD: C1_03.1, C2_03.1, J1_03.2, J2_03.2, R2_03.1, R5_03.1, R6_03.1, TP2_03.1, U1_03.4
B04/AUX_A1: TP5_04.1, U1_04.1
B04/AUX_PC7: TP6_04.1, U1_04.9
B04/GND: C1_04.2, C2_04.2, C3_04.2, J1_04.1, J1_04.MP, J2_04.1, J2_04.MP, RT1_04.2, TP3_04.1, U1_04.13
B04/LED_K: D1_04.1, U1_04.2
B04/NRST: TP4_04.1, U1_04.12
B04/NTC_ADC: C3_04.1, R1_04.2, RT1_04.1, U1_04.7
B04/NTC_DRV: R1_04.1, U1_04.8
B04/Net-(D1-A): D1_04.2, R2_04.2
B04/SCL_DN: J2_04.4, R4_04.2, R6_04.2, U1_04.6
B04/SCL_UP: J1_04.4, R4_04.1, TP1_04.1, U1_04.10
B04/SDA_DN: J2_04.3, R3_04.2, R5_04.2, U1_04.5
B04/SDA_UP: J1_04.3, R3_04.1, U1_04.3
B04/VDD: C1_04.1, C2_04.1, J1_04.2, J2_04.2, R2_04.1, R5_04.1, R6_04.1, TP2_04.1, U1_04.4
B05/AUX_A1: TP5_05.1, U1_05.1
B05/AUX_PC7: TP6_05.1, U1_05.9
B05/GND: C1_05.2, C2_05.2, C3_05.2, J1_05.1, J1_05.MP, J2_05.1, J2_05.MP, RT1_05.2, TP3_05.1, U1_05.13
B05/LED_K: D1_05.1, U1_05.2
B05/NRST: TP4_05.1, U1_05.12
B05/NTC_ADC: C3_05.1, R1_05.2, RT1_05.1, U1_05.7
B05/NTC_DRV: R1_05.1, U1_05.8
B05/Net-(D1-A): D1_05.2, R2_05.2
B05/SCL_DN: J2_05.4, R4_05.2, R6_05.2, U1_05.6
B05/SCL_UP: J1_05.4, R4_05.1, TP1_05.1, U1_05.10
B05/SDA_DN: J2_05.3, R3_05.2, R5_05.2, U1_05.5
B05/SDA_UP: J1_05.3, R3_05.1, U1_05.3
B05/VDD: C1_05.1, C2_05.1, J1_05.2, J2_05.2, R2_05.1, R5_05.1, R6_05.1, TP2_05.1, U1_05.4
B06/AUX_A1: TP5_06.1, U1_06.1
B06/AUX_PC7: TP6_06.1, U1_06.9
B06/GND: C1_06.2, C2_06.2, C3_06.2, J1_06.1, J1_06.MP, J2_06.1, J2_06.MP, RT1_06.2, TP3_06.1, U1_06.13
B06/LED_K: D1_06.1, U1_06.2
B06/NRST: TP4_06.1, U1_06.12
B06/NTC_ADC: C3_06.1, R1_06.2, RT1_06.1, U1_06.7
B06/NTC_DRV: R1_06.1, U1_06.8
B06/Net-(D1-A): D1_06.2, R2_06.2
B06/SCL_DN: J2_06.4, R4_06.2, R6_06.2, U1_06.6
B06/SCL_UP: J1_06.4, R4_06.1, TP1_06.1, U1_06.10
B06/SDA_DN: J2_06.3, R3_06.2, R5_06.2, U1_06.5
B06/SDA_UP: J1_06.3, R3_06.1, U1_06.3
B06/VDD: C1_06.1, C2_06.1, J1_06.2, J2_06.2, R2_06.1, R5_06.1, R6_06.1, TP2_06.1, U1_06.4
B07/AUX_A1: TP5_07.1, U1_07.1
B07/AUX_PC7: TP6_07.1, U1_07.9
B07/GND: C1_07.2, C2_07.2, C3_07.2, J1_07.1, J1_07.MP, J2_07.1, J2_07.MP, RT1_07.2, TP3_07.1, U1_07.13
B07/LED_K: D1_07.1, U1_07.2
B07/NRST: TP4_07.1, U1_07.12
B07/NTC_ADC: C3_07.1, R1_07.2, RT1_07.1, U1_07.7
B07/NTC_DRV: R1_07.1, U1_07.8
B07/Net-(D1-A): D1_07.2, R2_07.2
B07/SCL_DN: J2_07.4, R4_07.2, R6_07.2, U1_07.6
B07/SCL_UP: J1_07.4, R4_07.1, TP1_07.1, U1_07.10
B07/SDA_DN: J2_07.3, R3_07.2, R5_07.2, U1_07.5
B07/SDA_UP: J1_07.3, R3_07.1, U1_07.3
B07/VDD: C1_07.1, C2_07.1, J1_07.2, J2_07.2, R2_07.1, R5_07.1, R6_07.1, TP2_07.1, U1_07.4
B08/AUX_A1: TP5_08.1, U1_08.1
B08/AUX_PC7: TP6_08.1, U1_08.9
B08/GND: C1_08.2, C2_08.2, C3_08.2, J1_08.1, J1_08.MP, J2_08.1, J2_08.MP, RT1_08.2, TP3_08.1, U1_08.13
B08/LED_K: D1_08.1, U1_08.2
B08/NRST: TP4_08.1, U1_08.12
B08/NTC_ADC: C3_08.1, R1_08.2, RT1_08.1, U1_08.7
B08/NTC_DRV: R1_08.1, U1_08.8
B08/Net-(D1-A): D1_08.2, R2_08.2
B08/SCL_DN: J2_08.4, R4_08.2, R6_08.2, U1_08.6
B08/SCL_UP: J1_08.4, R4_08.1, TP1_08.1, U1_08.10
B08/SDA_DN: J2_08.3, R3_08.2, R5_08.2, U1_08.5
B08/SDA_UP: J1_08.3, R3_08.1, U1_08.3
B08/VDD: C1_08.1, C2_08.1, J1_08.2, J2_08.2, R2_08.1, R5_08.1, R6_08.1, TP2_08.1, U1_08.4
B09/AUX_A1: TP5_09.1, U1_09.1
B09/AUX_PC7: TP6_09.1, U1_09.9
B09/GND: C1_09.2, C2_09.2, C3_09.2, J1_09.1, J1_09.MP, J2_09.1, J2_09.MP, RT1_09.2, TP3_09.1, U1_09.13
B09/LED_K: D1_09.1, U1_09.2
B09/NRST: TP4_09.1, U1_09.12
B09/NTC_ADC: C3_09.1, R1_09.2, RT1_09.1, U1_09.7
B09/NTC_DRV: R1_09.1, U1_09.8
B09/Net-(D1-A): D1_09.2, R2_09.2
B09/SCL_DN: J2_09.4, R4_09.2, R6_09.2, U1_09.6
B09/SCL_UP: J1_09.4, R4_09.1, TP1_09.1, U1_09.10
B09/SDA_DN: J2_09.3, R3_09.2, R5_09.2, U1_09.5
B09/SDA_UP: J1_09.3, R3_09.1, U1_09.3
B09/VDD: C1_09.1, C2_09.1, J1_09.2, J2_09.2, R2_09.1, R5_09.1, R6_09.1, TP2_09.1, U1_09.4
B10/AUX_A1: TP5_10.1, U1_10.1
B10/AUX_PC7: TP6_10.1, U1_10.9
B10/GND: C1_10.2, C2_10.2, C3_10.2, J1_10.1, J1_10.MP, J2_10.1, J2_10.MP, RT1_10.2, TP3_10.1, U1_10.13
B10/LED_K: D1_10.1, U1_10.2
B10/NRST: TP4_10.1, U1_10.12
B10/NTC_ADC: C3_10.1, R1_10.2, RT1_10.1, U1_10.7
B10/NTC_DRV: R1_10.1, U1_10.8
B10/Net-(D1-A): D1_10.2, R2_10.2
B10/SCL_DN: J2_10.4, R4_10.2, R6_10.2, U1_10.6
B10/SCL_UP: J1_10.4, R4_10.1, TP1_10.1, U1_10.10
B10/SDA_DN: J2_10.3, R3_10.2, R5_10.2, U1_10.5
B10/SDA_UP: J1_10.3, R3_10.1, U1_10.3
B10/VDD: C1_10.1, C2_10.1, J1_10.2, J2_10.2, R2_10.1, R5_10.1, R6_10.1, TP2_10.1, U1_10.4
B11/AUX_A1: TP5_11.1, U1_11.1
B11/AUX_PC7: TP6_11.1, U1_11.9
B11/GND: C1_11.2, C2_11.2, C3_11.2, J1_11.1, J1_11.MP, J2_11.1, J2_11.MP, RT1_11.2, TP3_11.1, U1_11.13
B11/LED_K: D1_11.1, U1_11.2
B11/NRST: TP4_11.1, U1_11.12
B11/NTC_ADC: C3_11.1, R1_11.2, RT1_11.1, U1_11.7
B11/NTC_DRV: R1_11.1, U1_11.8
B11/Net-(D1-A): D1_11.2, R2_11.2
B11/SCL_DN: J2_11.4, R4_11.2, R6_11.2, U1_11.6
B11/SCL_UP: J1_11.4, R4_11.1, TP1_11.1, U1_11.10
B11/SDA_DN: J2_11.3, R3_11.2, R5_11.2, U1_11.5
B11/SDA_UP: J1_11.3, R3_11.1, U1_11.3
B11/VDD: C1_11.1, C2_11.1, J1_11.2, J2_11.2, R2_11.1, R5_11.1, R6_11.1, TP2_11.1, U1_11.4
B12/AUX_A1: TP5_12.1, U1_12.1
B12/AUX_PC7: TP6_12.1, U1_12.9
B12/GND: C1_12.2, C2_12.2, C3_12.2, J1_12.1, J1_12.MP, J2_12.1, J2_12.MP, RT1_12.2, TP3_12.1, U1_12.13
B12/LED_K: D1_12.1, U1_12.2
B12/NRST: TP4_12.1, U1_12.12
B12/NTC_ADC: C3_12.1, R1_12.2, RT1_12.1, U1_12.7
B12/NTC_DRV: R1_12.1, U1_12.8
B12/Net-(D1-A): D1_12.2, R2_12.2
B12/SCL_DN: J2_12.4, R4_12.2, R6_12.2, U1_12.6
B12/SCL_UP: J1_12.4, R4_12.1, TP1_12.1, U1_12.10
B12/SDA_DN: J2_12.3, R3_12.2, R5_12.2, U1_12.5
B12/SDA_UP: J1_12.3, R3_12.1, U1_12.3
B12/VDD: C1_12.1, C2_12.1, J1_12.2, J2_12.2, R2_12.1, R5_12.1, R6_12.1, TP2_12.1, U1_12.4
B13/AUX_A1: TP5_13.1, U1_13.1
B13/AUX_PC7: TP6_13.1, U1_13.9
B13/GND: C1_13.2, C2_13.2, C3_13.2, J1_13.1, J1_13.MP, J2_13.1, J2_13.MP, RT1_13.2, TP3_13.1, U1_13.13
B13/LED_K: D1_13.1, U1_13.2
B13/NRST: TP4_13.1, U1_13.12
B13/NTC_ADC: C3_13.1, R1_13.2, RT1_13.1, U1_13.7
B13/NTC_DRV: R1_13.1, U1_13.8
B13/Net-(D1-A): D1_13.2, R2_13.2
B13/SCL_DN: J2_13.4, R4_13.2, R6_13.2, U1_13.6
B13/SCL_UP: J1_13.4, R4_13.1, TP1_13.1, U1_13.10
B13/SDA_DN: J2_13.3, R3_13.2, R5_13.2, U1_13.5
B13/SDA_UP: J1_13.3, R3_13.1, U1_13.3
B13/VDD: C1_13.1, C2_13.1, J1_13.2, J2_13.2, R2_13.1, R5_13.1, R6_13.1, TP2_13.1, U1_13.4
B14/AUX_A1: TP5_14.1, U1_14.1
B14/AUX_PC7: TP6_14.1, U1_14.9
B14/GND: C1_14.2, C2_14.2, C3_14.2, J1_14.1, J1_14.MP, J2_14.1, J2_14.MP, RT1_14.2, TP3_14.1, U1_14.13
B14/LED_K: D1_14.1, U1_14.2
B14/NRST: TP4_14.1, U1_14.12
B14/NTC_ADC: C3_14.1, R1_14.2, RT1_14.1, U1_14.7
B14/NTC_DRV: R1_14.1, U1_14.8
B14/Net-(D1-A): D1_14.2, R2_14.2
B14/SCL_DN: J2_14.4, R4_14.2, R6_14.2, U1_14.6
B14/SCL_UP: J1_14.4, R4_14.1, TP1_14.1, U1_14.10
B14/SDA_DN: J2_14.3, R3_14.2, R5_14.2, U1_14.5
B14/SDA_UP: J1_14.3, R3_14.1, U1_14.3
B14/VDD: C1_14.1, C2_14.1, J1_14.2, J2_14.2, R2_14.1, R5_14.1, R6_14.1, TP2_14.1, U1_14.4
B15/AUX_A1: TP5_15.1, U1_15.1
B15/AUX_PC7: TP6_15.1, U1_15.9
B15/GND: C1_15.2, C2_15.2, C3_15.2, J1_15.1, J1_15.MP, J2_15.1, J2_15.MP, RT1_15.2, TP3_15.1, U1_15.13
B15/LED_K: D1_15.1, U1_15.2
B15/NRST: TP4_15.1, U1_15.12
B15/NTC_ADC: C3_15.1, R1_15.2, RT1_15.1, U1_15.7
B15/NTC_DRV: R1_15.1, U1_15.8
B15/Net-(D1-A): D1_15.2, R2_15.2
B15/SCL_DN: J2_15.4, R4_15.2, R6_15.2, U1_15.6
B15/SCL_UP: J1_15.4, R4_15.1, TP1_15.1, U1_15.10
B15/SDA_DN: J2_15.3, R3_15.2, R5_15.2, U1_15.5
B15/SDA_UP: J1_15.3, R3_15.1, U1_15.3
B15/VDD: C1_15.1, C2_15.1, J1_15.2, J2_15.2, R2_15.1, R5_15.1, R6_15.1, TP2_15.1, U1_15.4
B16/AUX_A1: TP5_16.1, U1_16.1
B16/AUX_PC7: TP6_16.1, U1_16.9
B16/GND: C1_16.2, C2_16.2, C3_16.2, J1_16.1, J1_16.MP, J2_16.1, J2_16.MP, RT1_16.2, TP3_16.1, U1_16.13
B16/LED_K: D1_16.1, U1_16.2
B16/NRST: TP4_16.1, U1_16.12
B16/NTC_ADC: C3_16.1, R1_16.2, RT1_16.1, U1_16.7
B16/NTC_DRV: R1_16.1, U1_16.8
B16/Net-(D1-A): D1_16.2, R2_16.2
B16/SCL_DN: J2_16.4, R4_16.2, R6_16.2, U1_16.6
B16/SCL_UP: J1_16.4, R4_16.1, TP1_16.1, U1_16.10
B16/SDA_DN: J2_16.3, R3_16.2, R5_16.2, U1_16.5
B16/SDA_UP: J1_16.3, R3_16.1, U1_16.3
B16/VDD: C1_16.1, C2_16.1, J1_16.2, J2_16.2, R2_16.1, R5_16.1, R6_16.1, TP2_16.1, U1_16.4
